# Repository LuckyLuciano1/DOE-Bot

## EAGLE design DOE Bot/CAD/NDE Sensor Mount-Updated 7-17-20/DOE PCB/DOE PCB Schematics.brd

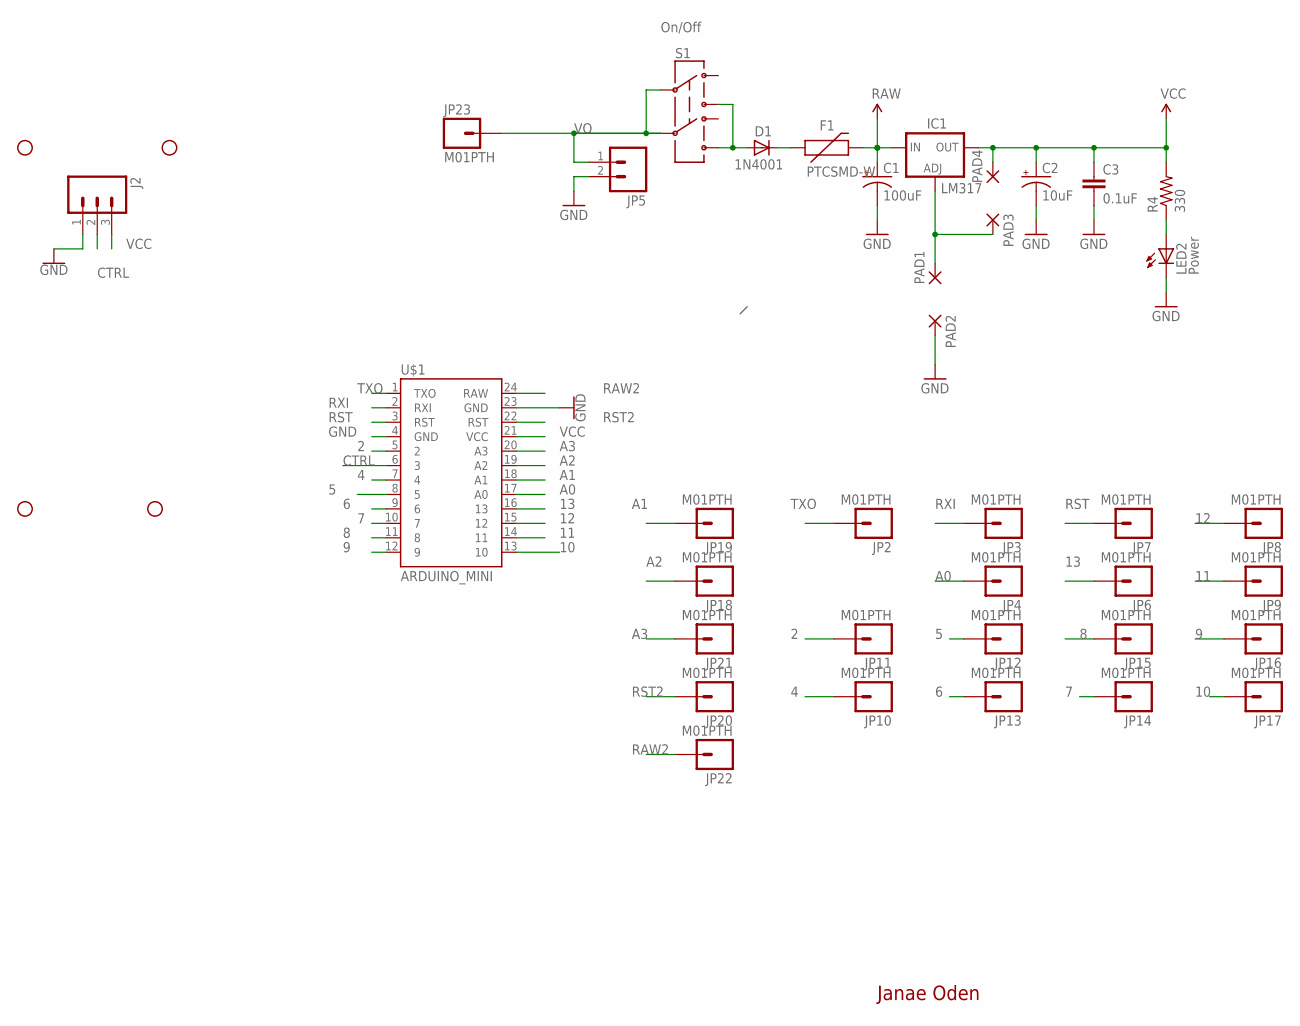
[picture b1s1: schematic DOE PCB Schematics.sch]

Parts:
C1: 100uF; EIA7343
C2: 10uF; EIA3216
C3: 0.1uF; 0603-CAP
D1: 1N4001; SMA-DIODE-TYLERALT1
F1: PTCSMD-W; PTC-1206-WIDE
IC1: LM317MBSTT3; SOT223; PARTNUMBER LM317
J2: M03SCREW; SCREWTERMINAL-3.5MM-3
JP2, JP3, JP4, JP6, JP7, JP8, JP9, JP10, JP11, JP12, JP13, JP14, JP15, JP16, JP17, JP18, JP19, JP20, JP21, JP22, JP23: M01PTH; 1X01
JP5: M02PTH; 1X02
LED2: Power; LED-1206
PAD1, PAD2, PAD3, PAD4: 1,6/0,8
R4: 330; 0603-RES
S1: On/Off; AYZ0202
U$1: ARDUINO_MINI
U$3, U$4, U$5, U$7: STAND-OFF

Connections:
2: JP11.1, U$1.5 (2)
4: JP10.1, U$1.7 (4)
5: JP12.1, U$1.8 (5)
6: JP13.1, U$1.9 (6)
7: JP14.1, U$1.10 (7)
8: JP15.1, U$1.11 (8)
9: JP16.1, U$1.12 (9)
10: JP17.1, U$1.13 (10)
11: JP9.1, U$1.14 (11)
12: JP8.1, U$1.15 (12)
13: JP6.1, U$1.16 (13)
A0: JP4.1, U$1.17 (A0)
A1: JP19.1, U$1.18 (A1)
A2: JP18.1, U$1.19 (A2)
A3: JP21.1, U$1.20 (A3)
CTRL: J2.2, U$1.6 (3)
GND: C1.C (-), C2.C (-), C3.2, J2.1, JP5.2, LED2.C, PAD2.1, U$1.4 (GND), U$1.23 (GND)
unnamed: D1.C, F1.1
unnamed: D1.A, S1.1 (3), S1.4 (6)
unnamed: IC1.1 (ADJ), PAD1.1, PAD3.1
unnamed: LED2.A, R4.1
RAW: C1.A (+), F1.2, IC1.3 (IN)
RAW2: JP22.1, U$1.24 (RAW)
RST: JP7.1, U$1.3 (RST)
RST2: JP20.1, U$1.22 (RST)
RXI: JP3.1, U$1.2 (RXI)
TXO: JP2.1, U$1.1 (TXO)
VCC: C2.A (+), C3.1, IC1.4 (OUT), J2.3, PAD4.1, R4.2, U$1.21 (VCC)
VO: JP5.1, JP23.1, S1.2, S1.5

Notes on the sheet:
Janae Oden

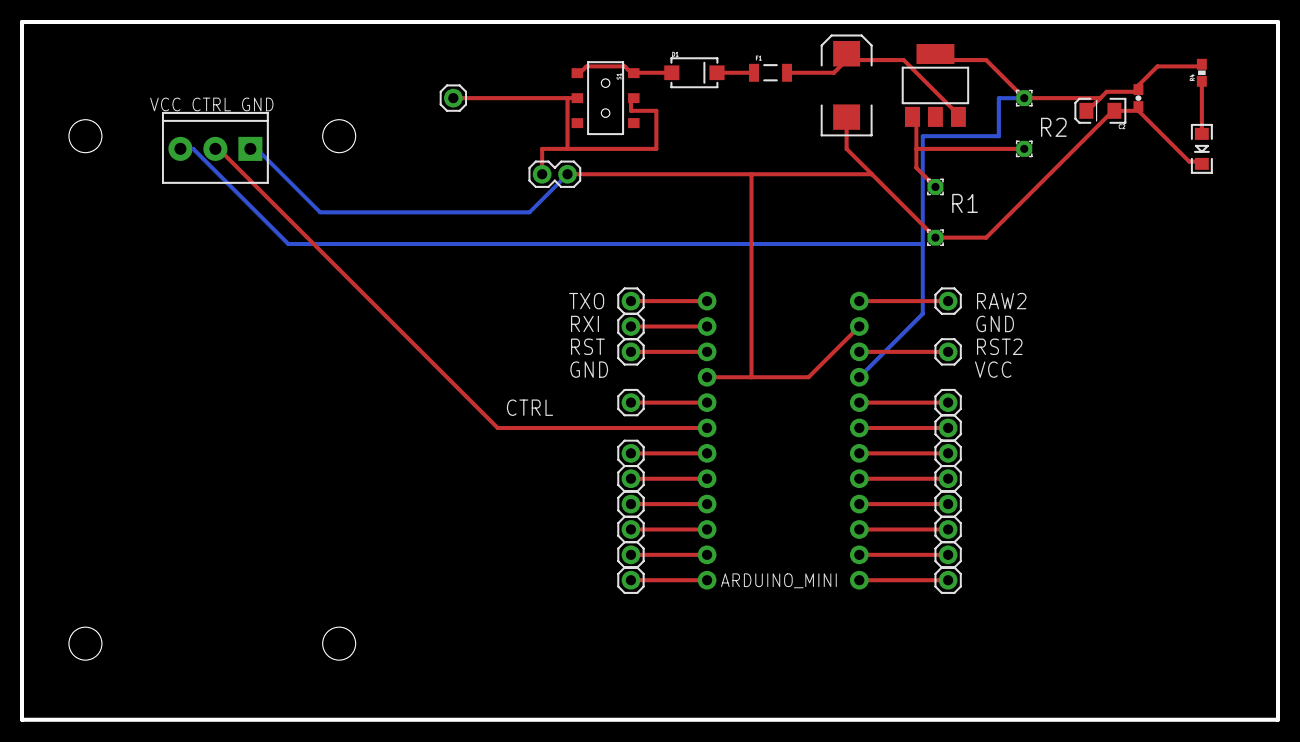
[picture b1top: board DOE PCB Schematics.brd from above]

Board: 2 copper layers, 125.7 x 69.8 mm, 41 parts (0 on the bottom side), 29 nets.

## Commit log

2020-09-28 9.28.2020
2020-10-20 10.19
2020-11-02 11.2.2020
2020-11-04 11.4.2020
2020-11-09 11.9.2020
2020-11-11 11.11.2020
2020-11-16 11.16.2020
2020-11-18 11.18.2020
2020-11-20 11.20.2020
2020-12-04 12.4.2020
2020-12-07 12.7.2020
2020-12-09 12.9.2020
2020-12-21 12.21.2020
2020-12-21 12.21.2020.2
2021-01-13 1.12.2020
2021-01-13 sdfg
2021-01-13 1.13.2021
2021-01-18 1.18
2021-01-28 1.28.2021
2021-02-02 2.1.2021
2021-02-02 8.51
2021-02-09 2.9.21
2021-02-20 2.20.2021
2021-03-03 3.2.2021
2021-03-05 3.4.2021
2021-03-18 3.18.2021
2021-03-23 3.23.2021
2021-03-24 3.24.2021
2021-06-02 6.1.2021

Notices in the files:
parts and their libraries:
SparkFun-PowerIC: Licensing: CC v3.0 Share-Alike You are welcome to use this library for commercial purposes.
SparkFun-Retired: Licensing: Creative Commons ShareAlike 4.0 International - https://creativecommons.org/licenses/by-sa/4.0
